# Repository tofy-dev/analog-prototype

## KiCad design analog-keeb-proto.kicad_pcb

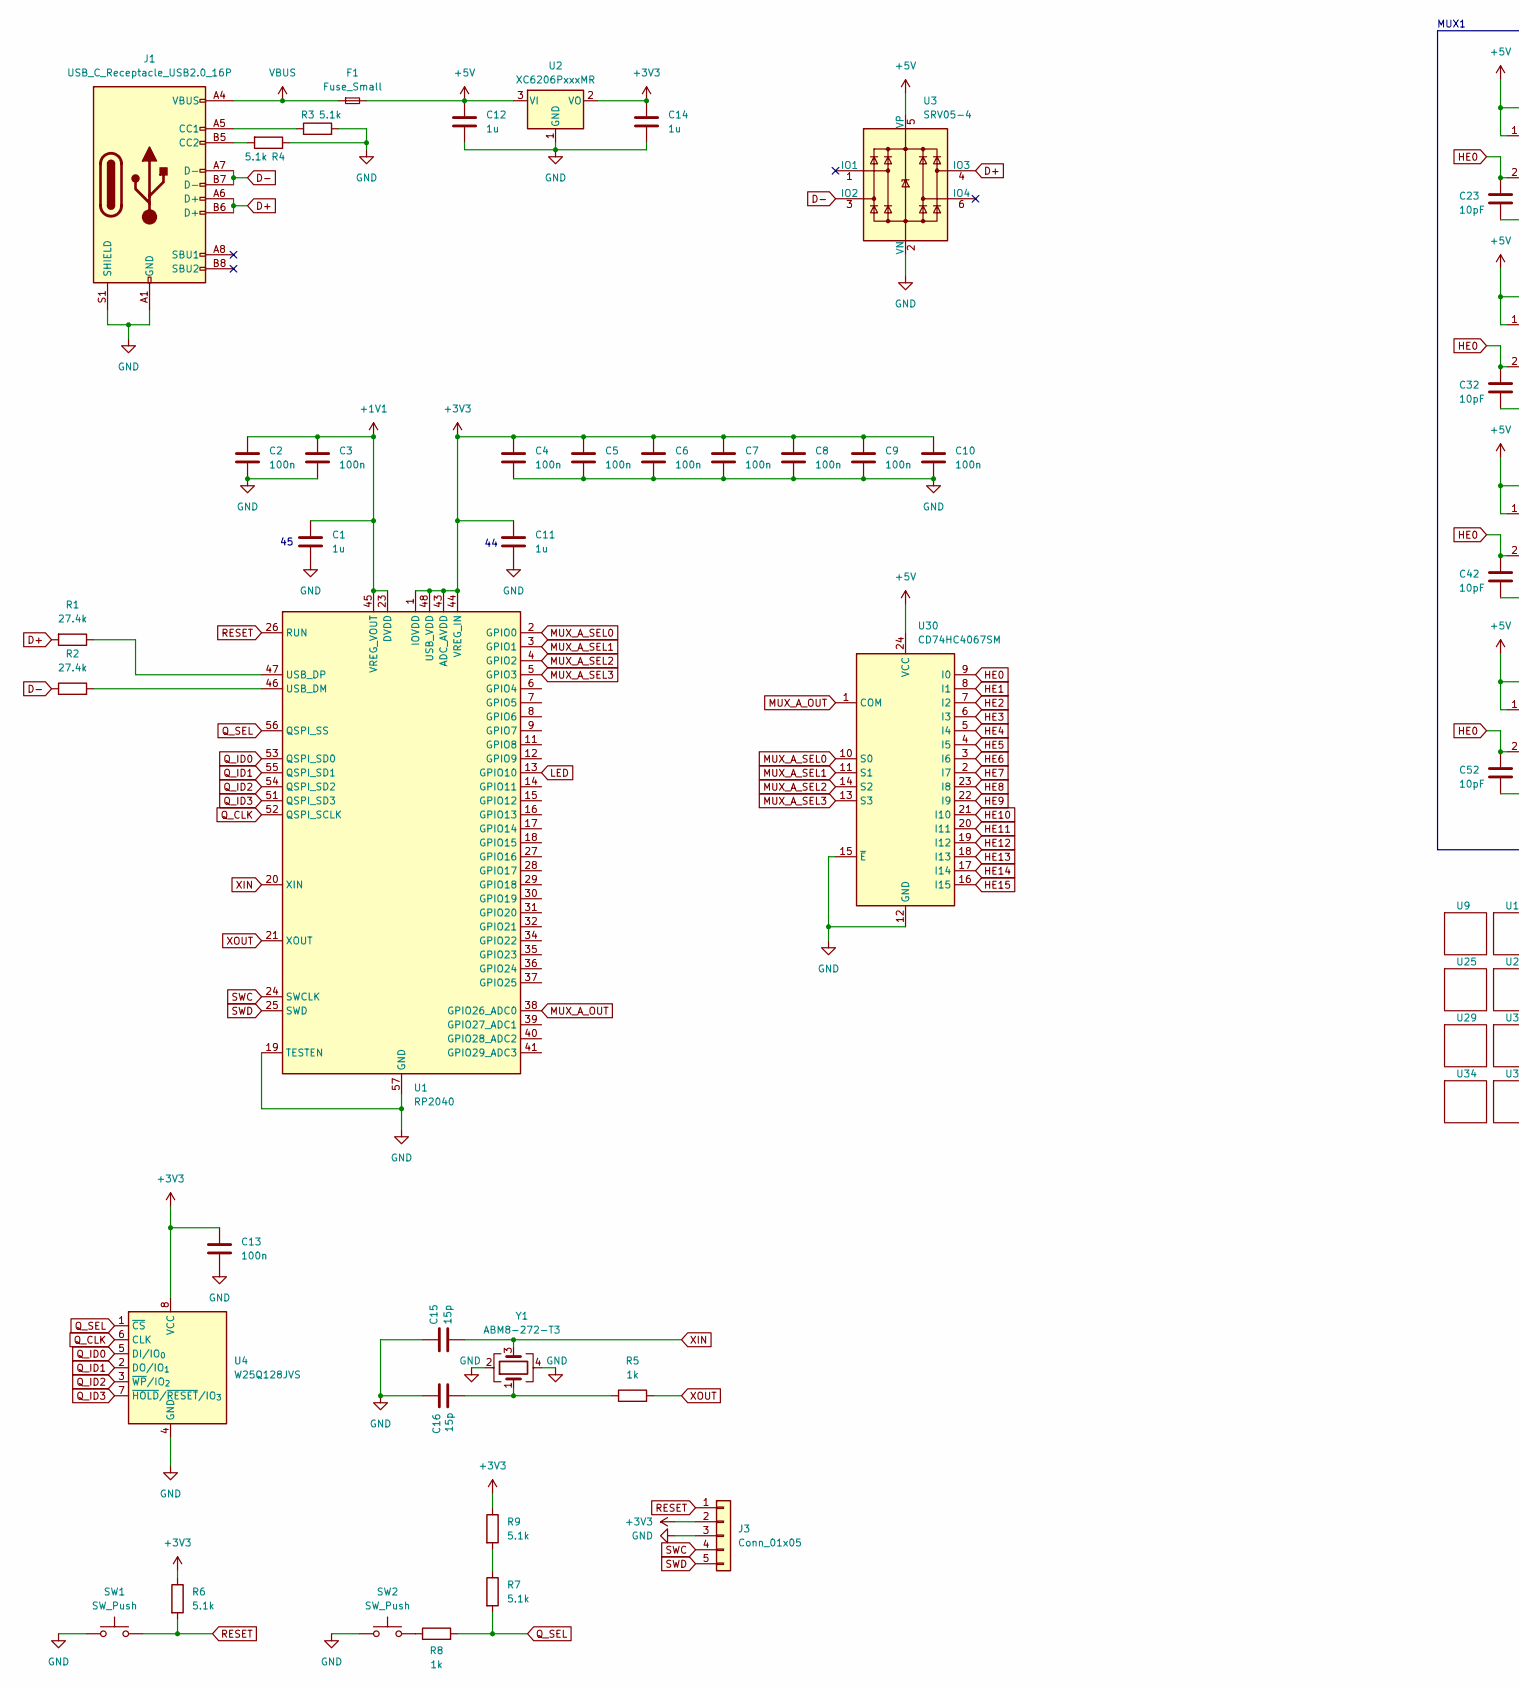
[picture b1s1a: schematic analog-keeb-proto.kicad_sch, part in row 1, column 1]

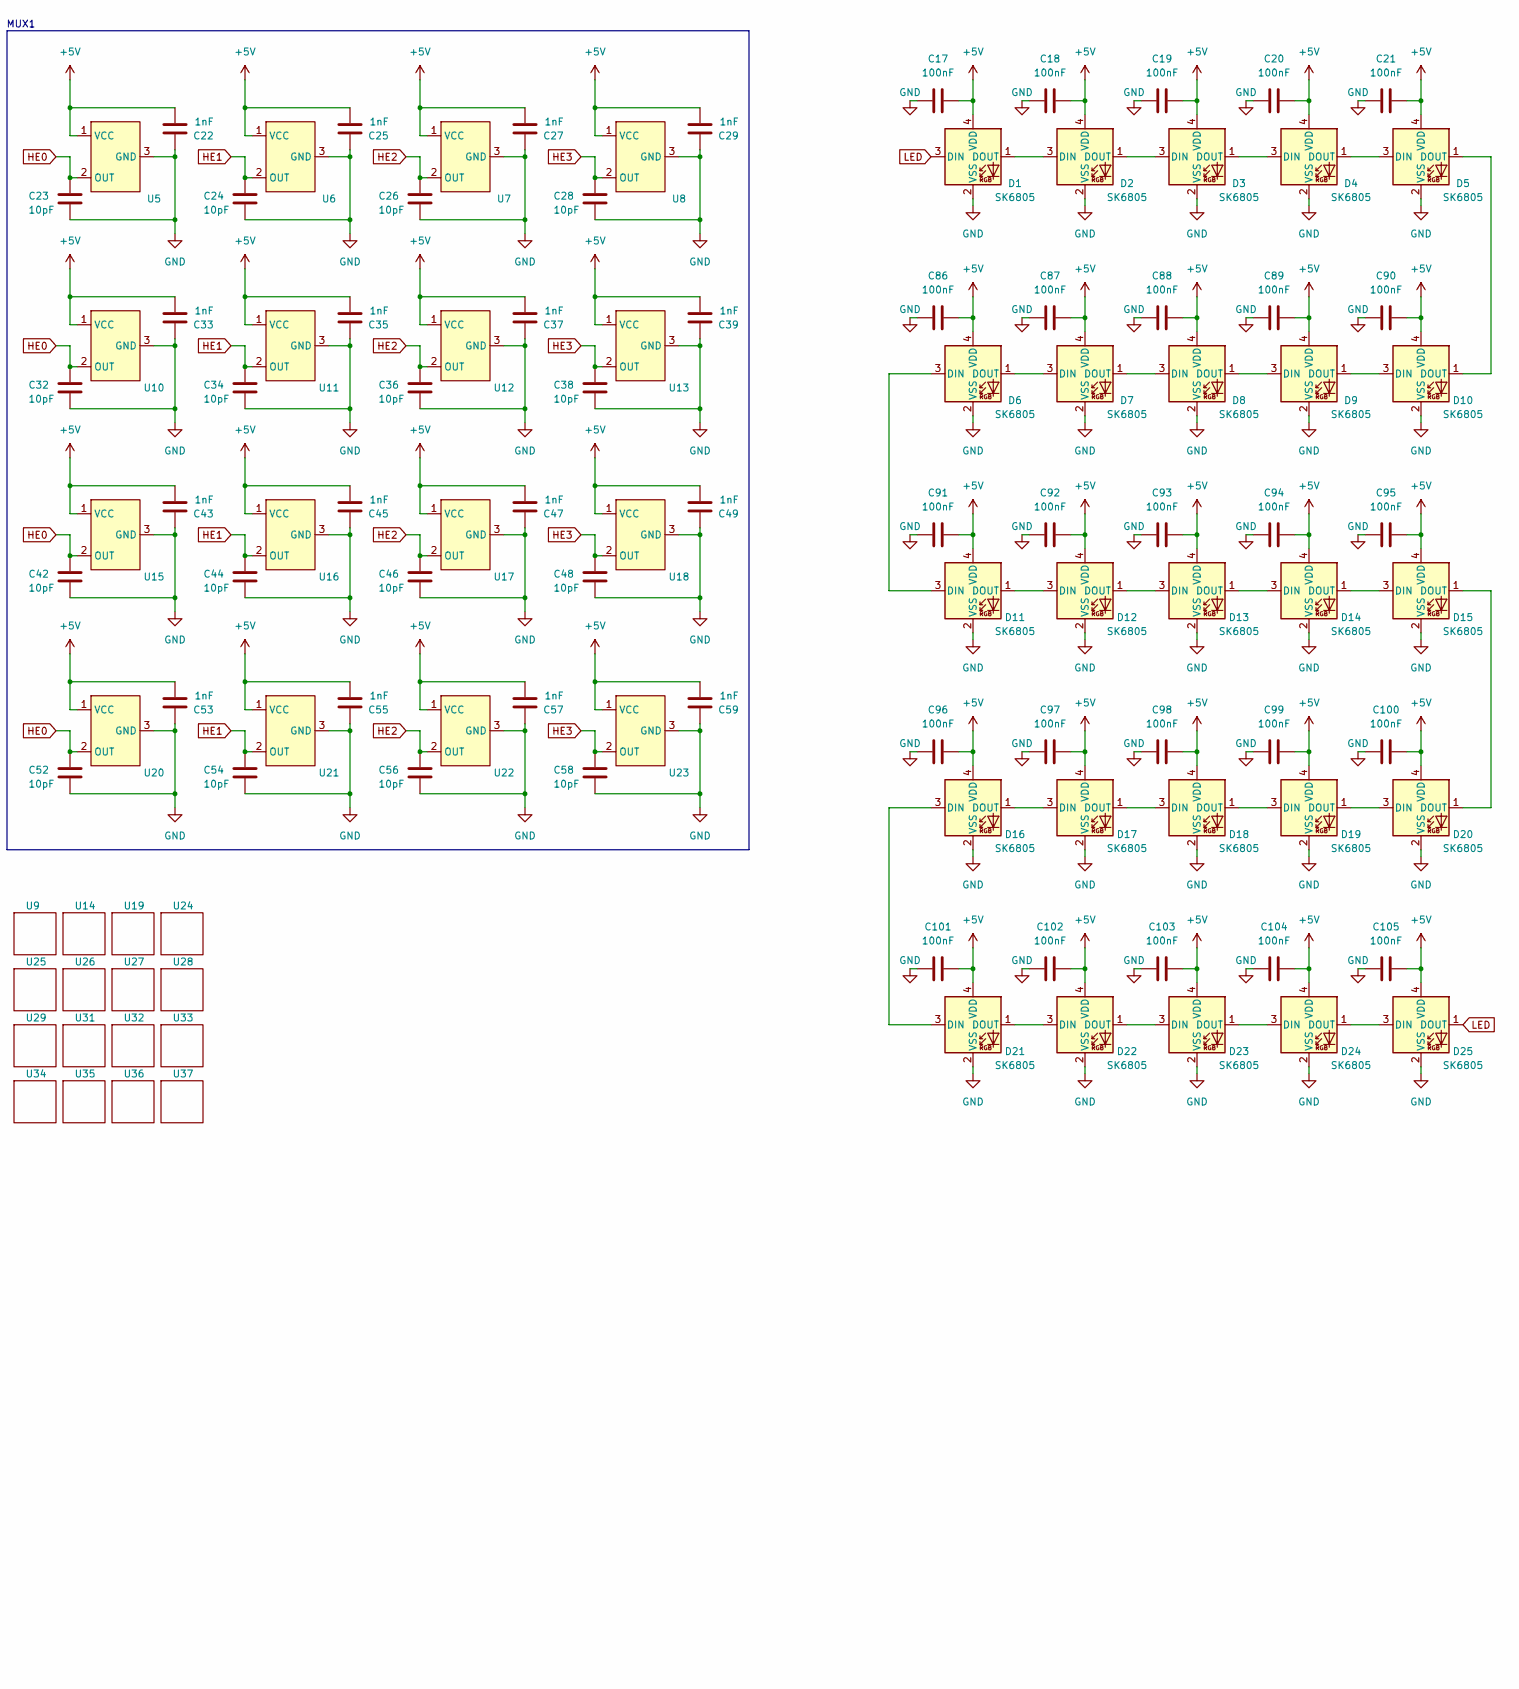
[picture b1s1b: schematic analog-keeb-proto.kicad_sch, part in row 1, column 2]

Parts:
C1, C11, C12, C14: 1u; C_01005_0402Metric
C2, C3, C4, C5, C6, C7, C8, C9, C10, C13: 100n; C_01005_0402Metric
C15, C16: 15p; C_01005_0402Metric
C17, C18, C19, C20, C21, C86, C87, C88, C89, C90, C91, C92, C93, C94, C95, C96, C97, C98, C99, C100, C101, C102, C103, C104, C105: 100nF; C_01005_0402Metric
C22, C25, C27, C29, C33, C35, C37, C39, C43, C45, C47, C49, C53, C55, C57, C59: 1nF; C_01005_0402Metric
C23, C24, C26, C28, C32, C34, C36, C38, C42, C44, C46, C48, C52, C54, C56, C58: 10pF; C_01005_0402Metric
D1, D2, D3, D4, D5, D6, D7, D8, D9, D10, D11, D12, D13, D14, D15, D16, D17, D18, D19, D20, D21, D22, D23, D24, D25: SK6805; LED_SK6805_PLCC4_2.4x2.7mm_P1.3mm
F1: Fuse_Small; Fuse_1206_3216Metric
J1: USB_C_Receptacle_USB2.0_16P; USB_C_Receptacle_HRO_TYPE-C-31-M-12
J3: Conn_01x05; PinHeader_1x05_P2.54mm_Vertical
R1, R2: 27.4k; R_0402_1005Metric
R3, R4, R6, R7, R9: 5.1k; R_0402_1005Metric
R5, R8: 1k; R_0402_1005Metric
SW1, SW2: SW_Push; SW_SPST_TL3342
U1: RP2040; QFN-56-1EP_7x7mm_P0.4mm_EP3.2x3.2mm
U2: XC6206PxxxMR; SOT-23-3
U3: SRV05-4; SOT-23-6
U4: W25Q128JVS; SOIC-8_5.3x5.3mm_P1.27mm
U5, U6, U7, U8, U10, U11, U12, U13, U15, U16, U17, U18, U20, U21, U22, U23: HX6659-SOT23
U9, U14, U19, U24, U25, U26, U27, U28, U29, U31, U32, U33, U34, U35, U36, U37: Gateron_1.00u
U30: CD74HC4067SM; SSOP-24_5.3x8.2mm_P0.65mm
Y1: ABM8-272-T3; Crystal_SMD_3225-4Pin_3.2x2.5mm

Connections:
+1V1: C1.2, C2.2, C3.2, U1.23 (DVDD), U1.45 (VREG_VOUT), U1.50 (DVDD)
+3V3: C4.2, C5.2, C6.2, C7.2, C8.2, C9.2, C10.2, C11.2, C13.2, C14.1, J3.2, R6.1, R9.1, U1.1 (IOVDD), U1.10 (IOVDD), U1.22 (IOVDD), U1.33 (IOVDD), U1.42 (IOVDD), U1.43 (ADC_AVDD), U1.44 (VREG_IN), U1.48 (USB_VDD), U1.49 (IOVDD), U2.2 (VO), U4.8 (VCC)
+5V: C12.1, C17.2, C18.2, C19.2, C20.2, C21.2, C22.1, C25.1, C27.1, C29.1, C33.1, C35.1, C37.1, C39.1, C43.1, C45.1, C47.1, C49.1, C53.1, C55.1, C57.1, C59.1, C86.2, C87.2, C88.2, C89.2, C90.2, C91.2, C92.2, C93.2, C94.2, C95.2, C96.2, C97.2, C98.2, C99.2, C100.2, C101.2, C102.2, C103.2, C104.2, C105.2, D1.4 (VDD), D2.4 (VDD), D3.4 (VDD), D4.4 (VDD), D5.4 (VDD), D6.4 (VDD), D7.4 (VDD), D8.4 (VDD), D9.4 (VDD), D10.4 (VDD), D11.4 (VDD), D12.4 (VDD), D13.4 (VDD), D14.4 (VDD), D15.4 (VDD), D16.4 (VDD), D17.4 (VDD), D18.4 (VDD), D19.4 (VDD), D20.4 (VDD), D21.4 (VDD), D22.4 (VDD), D23.4 (VDD), D24.4 (VDD), D25.4 (VDD), F1.2, U2.3 (VI), U3.5 (VP), U5.1 (VCC), U6.1 (VCC), U7.1 (VCC), U8.1 (VCC), U10.1 (VCC), U11.1 (VCC), U12.1 (VCC), U13.1 (VCC), U15.1 (VCC), U16.1 (VCC), U17.1 (VCC), U18.1 (VCC), U20.1 (VCC), U21.1 (VCC), U22.1 (VCC), U23.1 (VCC), U30.24 (VCC)
D+: J1.A6 (D+), J1.B6 (D+), R1.2, U3.4 (IO3)
D-: J1.A7 (D-), J1.B7 (D-), R2.1, U3.3 (IO2)
GND: C1.1, C2.1, C3.1, C4.1, C5.1, C6.1, C7.1, C8.1, C9.1, C10.1, C11.1, C12.2, C13.1, C14.2, C15.1, C16.1, C17.1, C18.1, C19.1, C20.1, C21.1, C22.2, C23.1, C24.1, C25.2, C26.1, C27.2, C28.1, C29.2, C32.1, C33.2, C34.1, C35.2, C36.1, C37.2, C38.1, C39.2, C42.1, C43.2, C44.1, C45.2, C46.1, C47.2, C48.1, C49.2, C52.1, C53.2, C54.1, C55.2, C56.1, C57.2, C58.1, C59.2, C86.1, C87.1, C88.1, C89.1, C90.1, C91.1, C92.1, C93.1, C94.1, C95.1, C96.1, C97.1, C98.1, C99.1, C100.1, C101.1, C102.1, C103.1, C104.1, C105.1, D1.2 (VSS), D2.2 (VSS), D3.2 (VSS), D4.2 (VSS), D5.2 (VSS), D6.2 (VSS), D7.2 (VSS), D8.2 (VSS), D9.2 (VSS), D10.2 (VSS), D11.2 (VSS), D12.2 (VSS), D13.2 (VSS), D14.2 (VSS), D15.2 (VSS), D16.2 (VSS), D17.2 (VSS), D18.2 (VSS), D19.2 (VSS), D20.2 (VSS), D21.2 (VSS), D22.2 (VSS), D23.2 (VSS), D24.2 (VSS), D25.2 (VSS), J1.A1 (GND), J1.A12 (GND), J1.B1 (GND), J1.B12 (GND), J1.S1 (SHIELD), J3.3, R3.2, R4.1, SW1.1, SW2.1, U1.19 (TESTEN), U1.57 (GND), U2.1 (GND), U3.2 (VN), U4.4 (GND), U5.3 (GND), U6.3 (GND), U7.3 (GND), U8.3 (GND), U10.3 (GND), U11.3 (GND), U12.3 (GND), U13.3 (GND), U15.3 (GND), U16.3 (GND), U17.3 (GND), U18.3 (GND), U20.3 (GND), U21.3 (GND), U22.3 (GND), U23.3 (GND), U30.12 (GND), U30.15 (~E), Y1.2, Y1.4
HE0: C23.2, C32.2, C42.2, C52.2, U5.2 (OUT), U10.2 (OUT), U15.2 (OUT), U20.2 (OUT), U30.9 (I0)
HE1: C24.2, C34.2, C44.2, C54.2, U6.2 (OUT), U11.2 (OUT), U16.2 (OUT), U21.2 (OUT), U30.8 (I1)
HE2: C26.2, C36.2, C46.2, C56.2, U7.2 (OUT), U12.2 (OUT), U17.2 (OUT), U22.2 (OUT), U30.7 (I2)
HE3: C28.2, C38.2, C48.2, C58.2, U8.2 (OUT), U13.2 (OUT), U18.2 (OUT), U23.2 (OUT), U30.6 (I3)
HE4: U30.5 (I4)
HE5: U30.4 (I5)
HE6: U30.3 (I6)
HE7: U30.2 (I7)
HE8: U30.23 (I8)
HE9: U30.22 (I9)
HE10: U30.21 (I10)
HE11: U30.20 (I11)
HE12: U30.19 (I12)
HE13: U30.18 (I13)
HE14: U30.17 (I14)
HE15: U30.16 (I15)
LED: D1.3 (DIN), D25.1 (DOUT), U1.13 (GPIO10)
MUX_A_OUT: U1.38 (GPIO26_ADC0), U30.1 (COM)
MUX_A_SEL0: U1.2 (GPIO0), U30.10 (S0)
MUX_A_SEL1: U1.3 (GPIO1), U30.11 (S1)
MUX_A_SEL2: U1.4 (GPIO2), U30.14 (S2)
MUX_A_SEL3: U1.5 (GPIO3), U30.13 (S3)
unnamed: C16.2, R5.1, Y1.1
unnamed: D1.1 (DOUT), D2.3 (DIN)
unnamed: D2.1 (DOUT), D3.3 (DIN)
unnamed: D3.1 (DOUT), D4.3 (DIN)
unnamed: D4.1 (DOUT), D5.3 (DIN)
unnamed: D6.1 (DOUT), D7.3 (DIN)
unnamed: D7.1 (DOUT), D8.3 (DIN)
unnamed: D8.1 (DOUT), D9.3 (DIN)
unnamed: D9.1 (DOUT), D10.3 (DIN)
unnamed: D5.1 (DOUT), D10.1 (DOUT)
unnamed: D6.3 (DIN), D11.3 (DIN)
unnamed: D11.1 (DOUT), D12.3 (DIN)
unnamed: D12.1 (DOUT), D13.3 (DIN)
unnamed: D13.1 (DOUT), D14.3 (DIN)
unnamed: D14.1 (DOUT), D15.3 (DIN)
unnamed: D15.1 (DOUT), D20.1 (DOUT)
unnamed: D16.3 (DIN), D21.3 (DIN)
unnamed: D16.1 (DOUT), D17.3 (DIN)
unnamed: D17.1 (DOUT), D18.3 (DIN)
unnamed: D18.1 (DOUT), D19.3 (DIN)
unnamed: D19.1 (DOUT), D20.3 (DIN)
unnamed: D21.1 (DOUT), D22.3 (DIN)
unnamed: D22.1 (DOUT), D23.3 (DIN)
unnamed: D23.1 (DOUT), D24.3 (DIN)
unnamed: D24.1 (DOUT), D25.3 (DIN)
unnamed: J1.A5 (CC1), R3.1
unnamed: J1.B5 (CC2), R4.2
unnamed: R7.1, R9.2
unnamed: R8.1, SW2.2
unnamed: R2.2, U1.46 (USB_DM)
unnamed: R1.1, U1.47 (USB_DP)
Q_CLK: U1.52 (QSPI_SCLK), U4.6 (CLK)
Q_ID0: U1.53 (QSPI_SD0), U4.5 (DI/IO_{0})
Q_ID1: U1.55 (QSPI_SD1), U4.2 (DO/IO_{1})
Q_ID2: U1.54 (QSPI_SD2), U4.3 (~WP/IO_{2})
Q_ID3: U1.51 (QSPI_SD3), U4.7 (~HOLD/~RESET/IO_{3})
Q_SEL: R7.2, R8.2, U1.56 (QSPI_SS), U4.1 (~CS)
RESET: J3.1, R6.2, SW1.2, U1.26 (RUN)
SWC: J3.4, U1.24 (SWCLK)
SWD: J3.5, U1.25 (SWD)
VBUS: F1.1, J1.A4 (VBUS), J1.A9 (VBUS), J1.B4 (VBUS), J1.B9 (VBUS)
XIN: C15.2, U1.20 (XIN), Y1.3
XOUT: R5.2, U1.21 (XOUT)

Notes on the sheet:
MUX1

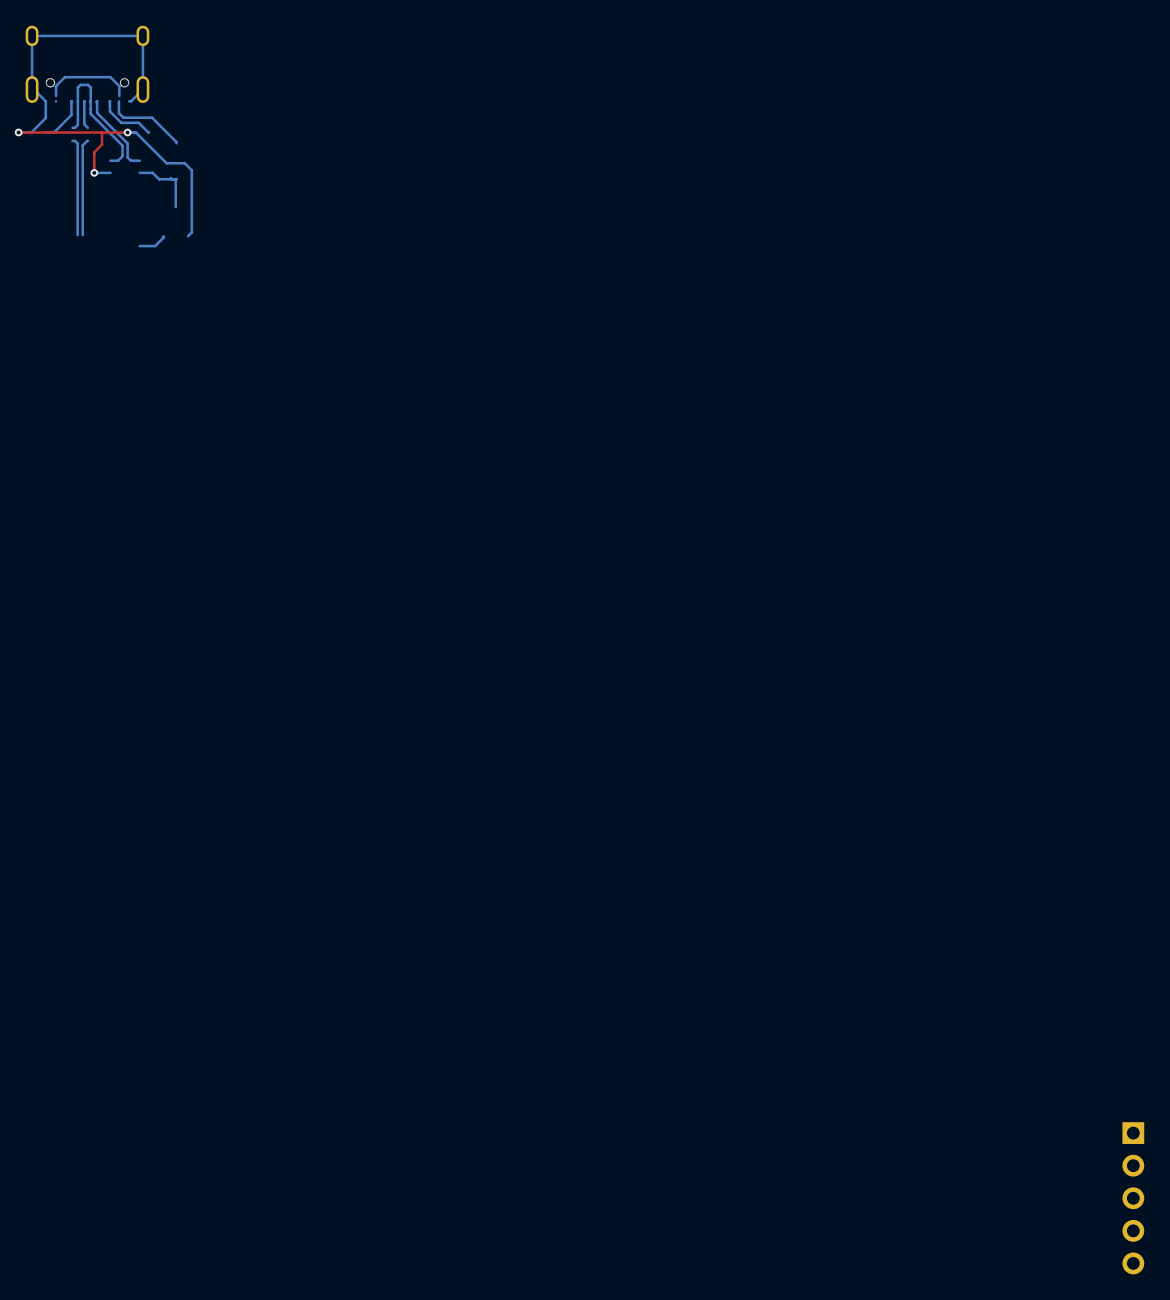
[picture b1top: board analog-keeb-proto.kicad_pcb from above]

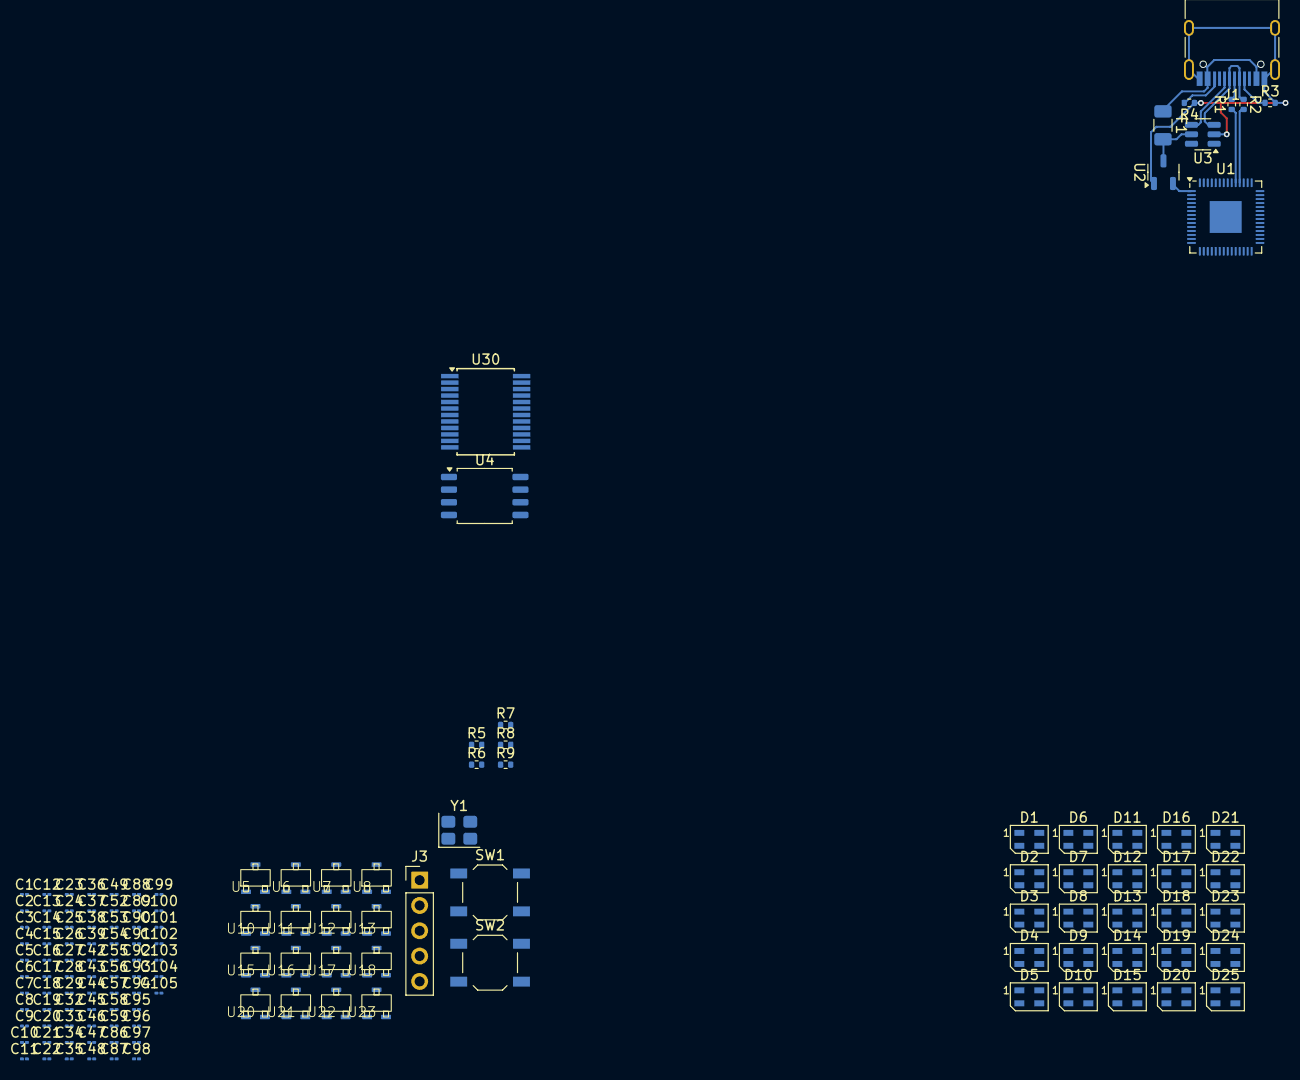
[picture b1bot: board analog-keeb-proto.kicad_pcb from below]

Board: 2 copper layers, 150 parts (150 on the bottom side), 59 nets.

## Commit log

2025-05-24 init
2025-05-25 add footprints
2025-05-25 finished schematic
2025-05-25 footprint stuff
2025-06-11 trol
